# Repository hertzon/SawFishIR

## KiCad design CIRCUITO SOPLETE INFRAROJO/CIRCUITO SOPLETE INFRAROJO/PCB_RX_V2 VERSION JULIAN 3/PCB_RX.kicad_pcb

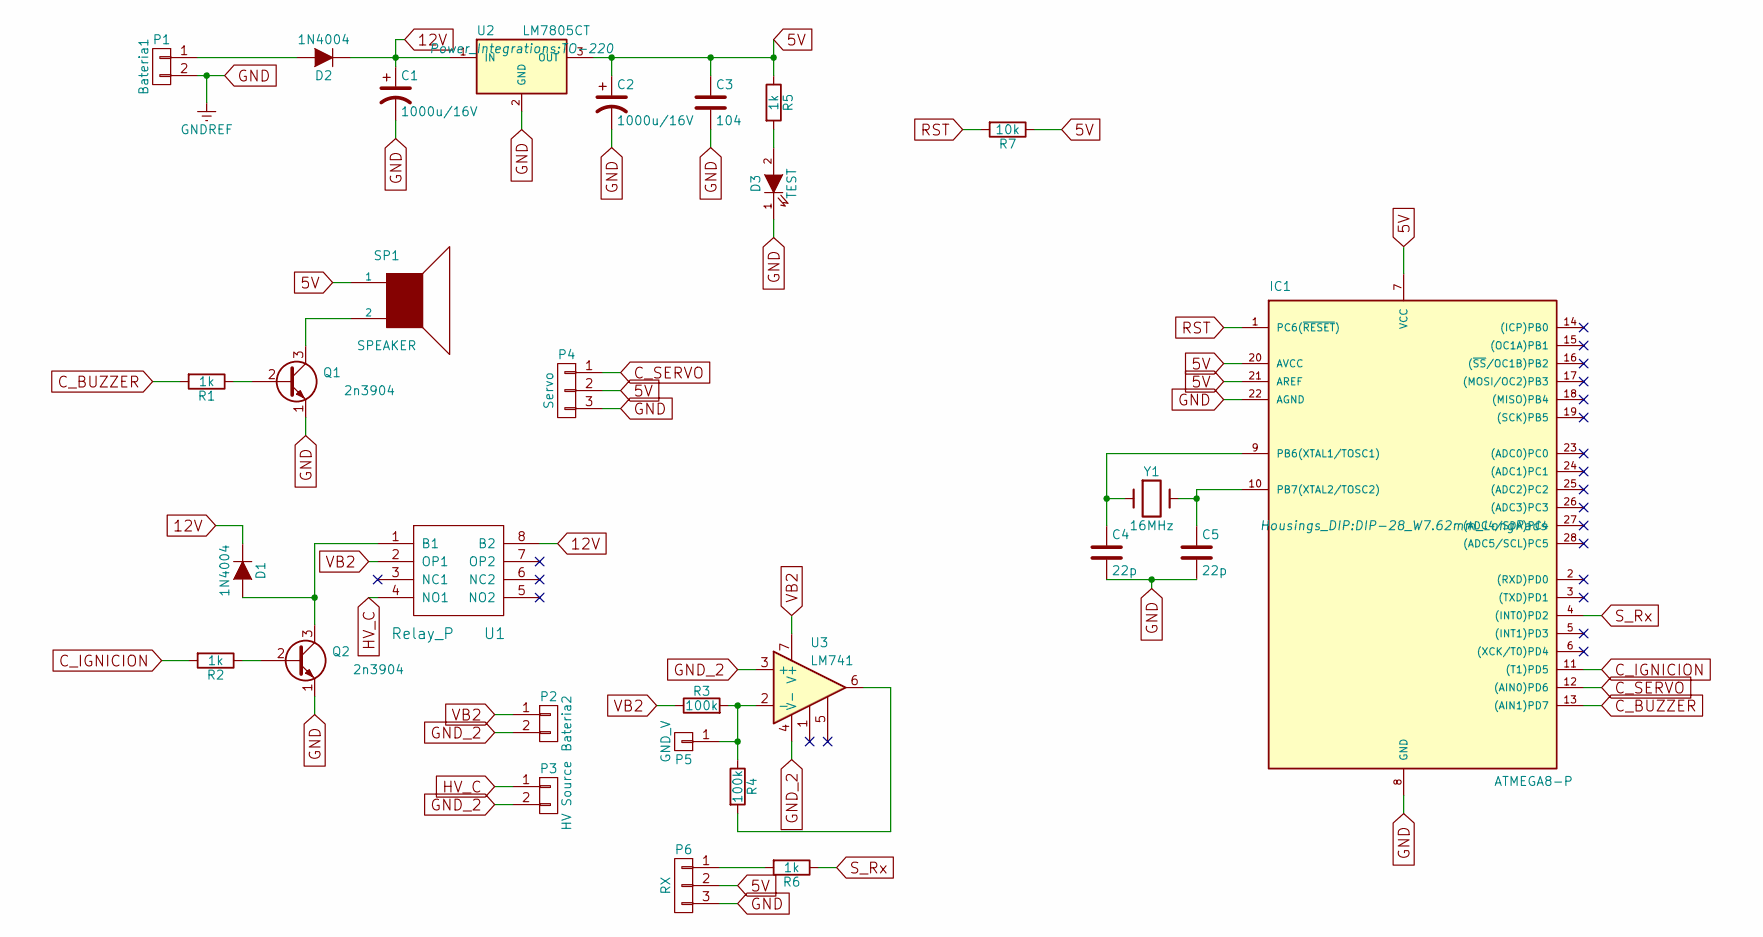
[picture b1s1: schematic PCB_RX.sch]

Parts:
C1, C2: 1000u/16V; CP_Radial_D10.0mm_P5.00mm
C3: 104; CP_Radial_D5.0mm_P2.50mm
C4, C5: 22p; CP_Radial_D5.0mm_P2.50mm
D1, D2: 1N4004; D_A-405_P5.08mm_Vertical_AnodeUp
D3: TEST; LED_D5.0mm
IC1: ATMEGA8-P; DIP-28_W7.62mm_LongPads
P1: Bateria1; bornier2
P2: Bateria2; bornier2
P3: HV Source; bornier2
P4: Servo; AK300-3
P5: GND_V; PINTST
P6: RX; Molex_KK-6410-03_03x2.54mm_Straight
Q1, Q2: 2n3904; TO-92_Molded_Narrow_Oval
R1: 1k; R_Axial_DIN0204_L3.6mm_D1.6mm_P7.62mm_Horizontal
R2: 1k; R_Axial_DIN0204_L3.6mm_D1.6mm_P5.08mm_Horizontal
R3, R4: 100k; R_Axial_DIN0204_L3.6mm_D1.6mm_P2.54mm_Vertical
R5, R6: 1k; R_Axial_DIN0204_L3.6mm_D1.6mm_P2.54mm_Vertical
R7: 10k; R_Axial_DIN0204_L3.6mm_D1.6mm_P2.54mm_Vertical
SP1: SPEAKER; Buzzer_12x9.5RM7.6
U1: Relay_P; HK19F
U2: LM7805CT; TO-220
U3: LM741; DIP-8_W7.62mm_LongPads
Y1: 16MHz; Crystal_HC18-U_Vertical

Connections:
5V: C2.1, C3.1, IC1.7 (VCC), IC1.20 (AVCC), IC1.21 (AREF), P4.2, P6.2, R5.1, R7.1, SP1.1, U2.3 (OUT)
12V: C1.1, D1.1 (K), D2.1 (K), U1.8 (B2), U2.1 (IN)
C_BUZZER: IC1.13 ((AIN1)PD7), R1.2
C_IGNICION: IC1.11 ((T1)PD5), R2.2
C_SERVO: IC1.12 ((AIN0)PD6), P4.1
GND: C1.2, C2.2, C3.2, C4.2, C5.2, D3.1 (K), IC1.8 (GND), IC1.22 (AGND), P1.2, P4.3, P6.3, Q1.1 (E), Q2.1 (E), U2.2 (GND)
GND_2: P2.2, P3.2, U3.3 (+), U3.4 (V-)
HV_C: P3.1, U1.4 (NO1)
unnamed: C4.1, IC1.9 (PB6(XTAL1/TOSC1)), Y1.1
unnamed: C5.1, IC1.10 (PB7(XTAL2/TOSC2)), Y1.2
unnamed: D1.2 (A), Q2.3 (C), U1.1 (B1)
unnamed: D2.2 (A), P1.1
unnamed: D3.2 (A), R5.2
unnamed: P5.1, R3.2, R4.1, U3.2 (-)
unnamed: P6.1, R6.2
unnamed: Q1.2 (B), R1.1
unnamed: Q1.3 (C), SP1.2
unnamed: Q2.2 (B), R2.1
unnamed: R4.2, U3.6
RST: IC1.1 (PC6(~RESET~)), R7.2
S_Rx: IC1.4 ((INT0)PD2), R6.1
VB2: P2.1, R3.1, U1.2 (OP1), U3.7 (V+)

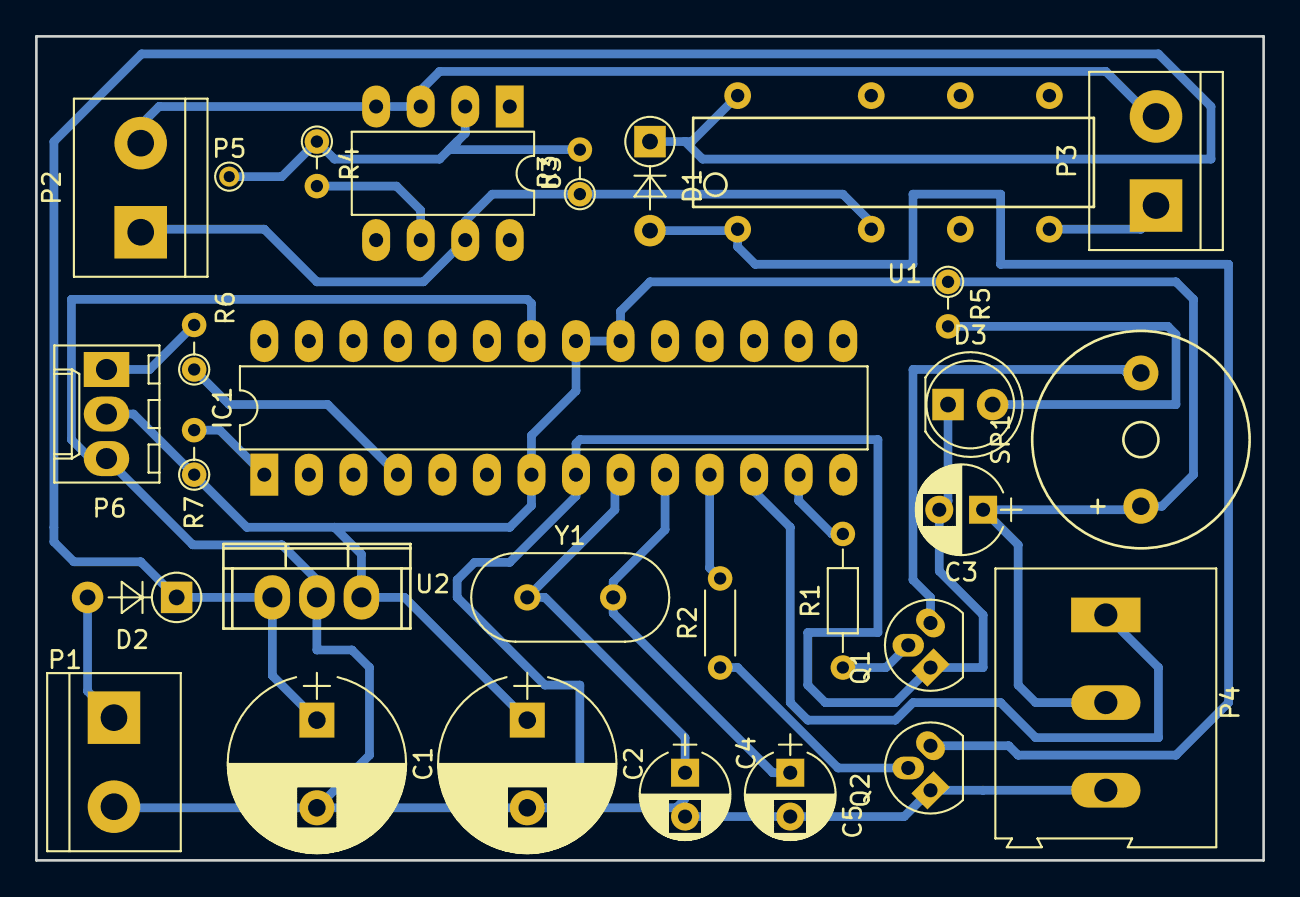
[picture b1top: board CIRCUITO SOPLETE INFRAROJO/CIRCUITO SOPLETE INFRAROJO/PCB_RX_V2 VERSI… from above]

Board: 2 copper layers, 70.0 x 47.0 mm, 29 parts (0 on the bottom side), 22 nets.

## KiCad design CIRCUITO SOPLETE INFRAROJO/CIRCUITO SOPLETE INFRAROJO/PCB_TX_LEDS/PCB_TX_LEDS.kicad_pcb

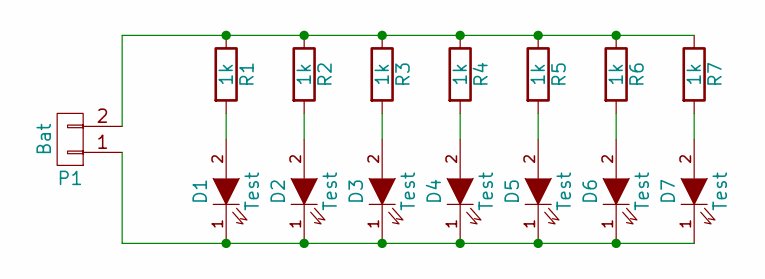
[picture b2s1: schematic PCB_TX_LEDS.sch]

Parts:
D1, D2, D3, D4, D5, D6, D7: Test; LED_D5.0mm
P1: Bat; AK300-2
R1, R2, R3, R4, R5, R6, R7: 1k; R_Axial_DIN0207_L6.3mm_D2.5mm_P7.62mm_Horizontal

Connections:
unnamed: D1.1 (K), D2.1 (K), D3.1 (K), D4.1 (K), D5.1 (K), D6.1 (K), D7.1 (K), P1.1
unnamed: D1.2 (A), R1.2
unnamed: D2.2 (A), R2.2
unnamed: D3.2 (A), R3.2
unnamed: D4.2 (A), R4.2
unnamed: D5.2 (A), R5.2
unnamed: D6.2 (A), R6.2
unnamed: D7.2 (A), R7.2
unnamed: P1.2, R1.1, R2.1, R3.1, R4.1, R5.1, R6.1, R7.1

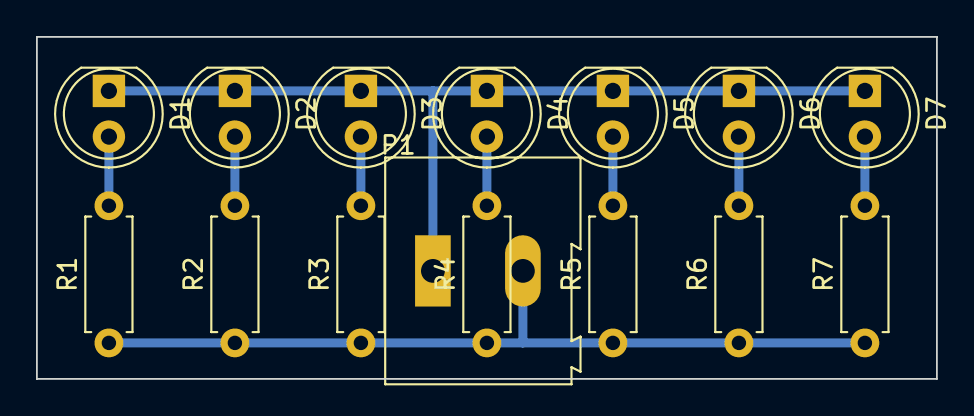
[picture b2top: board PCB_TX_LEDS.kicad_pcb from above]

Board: 2 copper layers, 50.0 x 19.0 mm, 15 parts (0 on the bottom side), 9 nets.

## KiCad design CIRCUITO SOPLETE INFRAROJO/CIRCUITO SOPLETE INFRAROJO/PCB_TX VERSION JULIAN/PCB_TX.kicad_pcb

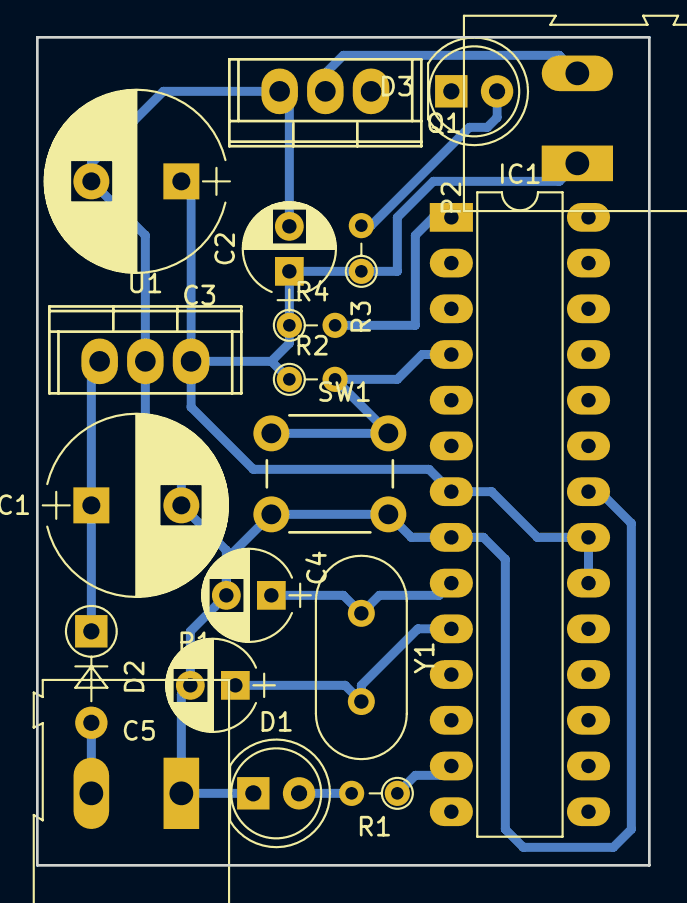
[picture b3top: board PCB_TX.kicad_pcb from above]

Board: 2 copper layers, 34.0 x 46.0 mm, 19 parts (0 on the bottom side), 12 nets.

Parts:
C1, C3: 1000u/16V; CP_Radial_D10.0mm_P5.00mm
C2: 104; CP_Radial_D5.0mm_P2.50mm
C4, C5: 22p; CP_Radial_D5.0mm_P2.50mm
D1, D3: Test; LED_D5.0mm
D2: 1n4004; D_A-405_P5.08mm_Vertical_AnodeUp
IC1: ATMEGA8-P; DIP-28_W7.62mm_LongPads
P1: Bat; AK300-2
P2: LEDS OUTPUT; AK300-2
Q1: IRF540N; TO-220
R1, R3: 1k; R_Axial_DIN0204_L3.6mm_D1.6mm_P2.54mm_Vertical
R2, R4: 10k; R_Axial_DIN0204_L3.6mm_D1.6mm_P2.54mm_Vertical
SW1: Pulsador; SW_PUSH_6mm_h5mm
U1: LM78M05CT; TO-220
Y1: 16MHz; Crystal_HC18-U_Vertical

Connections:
5V: C2.1, C3.1, IC1.7, IC1.20, IC1.21, P2.1, R2.1, R3.1, R4.1, U1.3
12V: C1.1, D2.1, U1.1
C_Pulse: IC1.4, R2.2, SW1.1
C_TESTIGO: IC1.13, R1.1
GND: C1.2, C2.2, C3.2, C4.2, C5.2, D1.1, D3.1, IC1.8, IC1.22, P1.1, Q1.3, SW1.2, U1.2
unnamed: C4.1, IC1.9, Y1.1
unnamed: C5.1, IC1.10, Y1.2
unnamed: D1.2, R1.2
unnamed: D2.2, P1.2
unnamed: D3.2, R3.2
unnamed: P2.2, Q1.2
RESET: IC1.1, R4.2

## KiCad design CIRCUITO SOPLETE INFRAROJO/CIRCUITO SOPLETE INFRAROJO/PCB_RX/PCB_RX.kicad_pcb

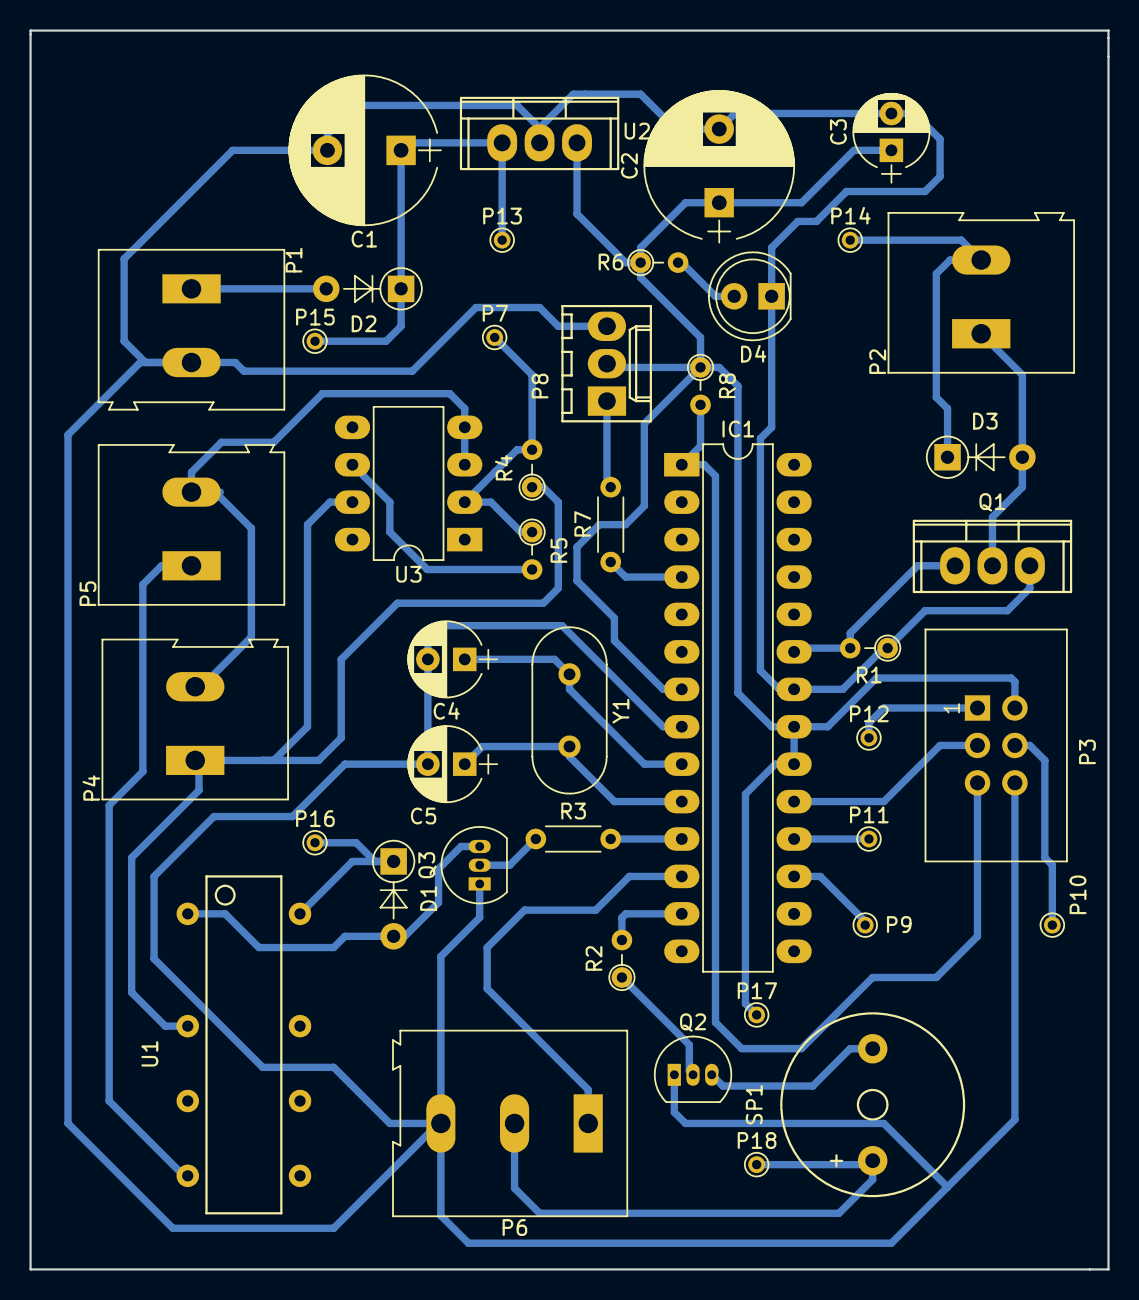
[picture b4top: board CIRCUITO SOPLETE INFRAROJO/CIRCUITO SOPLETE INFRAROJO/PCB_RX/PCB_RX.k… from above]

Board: 2 copper layers, 73.2 x 84.1 mm, 44 parts (0 on the bottom side), 32 nets.

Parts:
C1, C2: 1000u/16V; CP_Radial_D10.0mm_P5.00mm
C3: 104; CP_Radial_D5.0mm_P2.50mm
C4, C5: 22p; CP_Radial_D5.0mm_P2.50mm
D1, D2, D3: 1N4004; D_A-405_P5.08mm_Vertical_AnodeUp
D4: TEST; LED_D5.0mm
IC1: ATMEGA8-P; DIP-28_W7.62mm_LongPads
P1: Bateria1; AK300-2
P2: SEL; AK300-2
P3: PROG; IDC_Header_Straight_6pins
P4: Bateria2; AK300-2
P5: HV Source; AK300-2
P6: Servo; AK300-3
P7: GND_V; PINTST
P8: RX; Molex_KK-6410-03_03x2.54mm_Straight
P9: PB3_1; PINTST
P10: PB3_2; PINTST
P11: PB4_1; PINTST
P12: PB4_2; PINTST
P13, P15: 12V; PINTST
P14: 12V_1; PINTST
P16: 12V_2; PINTST
P17: 5V; PINTST
P18: 5V_1; PINTST
Q1: IRF540N; TO-220
Q2, Q3: 2n3904; TO-92_Inline_Narrow_Oval
R1, R8: 10k; R_Axial_DIN0204_L3.6mm_D1.6mm_P2.54mm_Vertical
R2, R6: 1k; R_Axial_DIN0204_L3.6mm_D1.6mm_P2.54mm_Vertical
R3, R7: 1k; R_Axial_DIN0204_L3.6mm_D1.6mm_P5.08mm_Horizontal
R4, R5: 100k; R_Axial_DIN0204_L3.6mm_D1.6mm_P2.54mm_Vertical
SP1: SPEAKER; Buzzer_12x9.5RM7.6
U1: Relay_P; HK19F
U2: LM7805CT; TO-220
U3: LM741; DIP-8_W7.62mm_LongPads
Y1: 16MHz; Crystal_HC18-U_Vertical

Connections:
5V: C2.1, C3.1, IC1.7, IC1.20, IC1.21, P3.2, P8.2, P17.1, R6.1, R8.1, U2.3
5V_1: P6.2, P18.1, SP1.1
12V: C1.1, D2.1, P13.1, P15.1, U2.1
12V_1: D3.1, P2.2, P14.1
12V_2: D1.1, P16.1, U1.8
C_BUZZER: IC1.13, R2.2
C_IGNICION: IC1.11, R3.2
C_SEL: IC1.23, Q1.1, R1.2
C_SERVO: IC1.12, P6.1
GND: C1.2, C2.2, C3.2, C4.2, C5.2, D4.1, IC1.8, IC1.22, P1.2, P3.6, P6.3, P8.3, Q1.3, Q2.1, Q3.1, R1.1, U2.2
GND_2: P4.2, P5.2, U3.3, U3.4
HV_C: P5.1, U1.4
unnamed: C4.1, IC1.9, Y1.1
unnamed: C5.1, IC1.10, Y1.2
unnamed: D1.2, Q3.3, U1.1
unnamed: D2.2, P1.1
unnamed: D3.2, P2.1, Q1.2
unnamed: D4.2, R6.2
unnamed: P7.1, R4.2, R5.1, U3.2
unnamed: P8.1, R7.2
unnamed: Q2.2, R2.1
unnamed: Q2.3, SP1.2
unnamed: Q3.2, R3.1
unnamed: R5.2, U3.6
PB3: IC1.17, P9.1
PB3_2: P3.4, P10.1
PB4: IC1.18, P11.1
PB4_2: P3.1, P12.1
PB5: IC1.19, P3.3
RST: IC1.1, P3.5, R8.2
S_Rx: IC1.4, R7.1
VB2: P4.1, R4.1, U1.2, U3.7

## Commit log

2017-05-22 first commit 21/05/2071
2017-05-24 23/05/2017
2017-05-29 28/05/2017
2017-06-22 21/06/2017
2017-07-06 05/07/2017
2017-07-22 22/07/2017
2017-07-23 version 2
